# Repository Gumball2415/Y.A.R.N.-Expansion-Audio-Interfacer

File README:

# Y.A.R.N. Expansion Audio Interfacer

An Open-Source HardWare (OSHW) Famicom single expansion audio interfacer.

This project aims to allow a host cartridge to control an expansion audio cartridge's sound chip. This is a child of the S.C.A.R.F. project.

Currently a work in progress.

## PCB Specifications

W.I.P.

## License

- The PCB and schematics are licensed under the TAPR Open Hardware License ([www.tapr.org/OHL](http://www.tapr.org/OHL)).
- The PLD source code files are licensed under GPL 2.0 or higher. (https://www.gnu.org/licenses/old-licenses/gpl-2.0.html)
- © Persune 2021

## Credits

- lidnariq, grievre, Iyatemu, and plgDavid - advice, suggestions, general help
- lidnariq - providing advice for my schematics and addressing logic
- grievre - providing advice for my PCB design
- Special thanks to the NESDEV community, this project wouldn't have been possible without their extensive information and wiki!

## Support

Support me on [Ko-Fi](https://ko-fi.com/persune) to help me afford hardware development equipment and further improve this project!

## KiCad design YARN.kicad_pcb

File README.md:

# Y.A.R.N. Expansion Audio Interfacer

An Open-Source HardWare (OSHW) Famicom single expansion audio interfacer.

## About

This project aims to allow a host cartridge to control an expansion audio cartridge's sound chip through selected audio registers. This is a child of the S.C.A.R.F. project.

The principle is that the Main cartridge is expected to contain everything the NSF or program needs, with the audio solely being handled by the Exp audio cartridge.

This means that the expansion audio cartridge is write-only.

## Use

The Main cartridge is expected to contain mapper hardware that the NSF or program needs.

The Console is expected to not read the Exp. cartridge, but instead to write to registers the Exp. cartridge is expected to contain.

The Exp. cartridge must contain hardware that generates audio accessible by write-only registers that the Console expects.

If the Exp. cartridge contains VRC6B, toggle SW2 accordingly.

Do not toggle SW1, it is for prototyping purposes.

For Everdrives and flash carts: The flash cart UI (if it has one) may cause unwanted side effects if it is connected to YARN.

## PCB Specifications

- 2 layer PCB
- 1.2mm thickness
- ENIG-RoHS surface finish recommended; Gold fingers optional
- Beveled edge, chamfer cut
- Any soldermask color you want!

## License

- The PCB and schematics are licensed under the TAPR Open Hardware License ([www.tapr.org/OHL](http://www.tapr.org/OHL)).
- The S.C.A.R.F. Expansion Audio Interfacer Address Decoder ROM source code file is licensed under [MIT](https://mit-license.org/)
- © Persune 2022

## Credits

- lidnariq, grievre, Iyatemu, and plgDavid - advice, suggestions, general help
- lidnariq - providing advice for my schematics and addressing logic
- grievre - providing advice for my PCB design
- Special thanks to the NESDEV community, this project wouldn't have been possible without their extensive information and wiki!

## Support

If you enjoy this project or find it helpful, please support me on [Ko-Fi](https://ko-fi.com/persune) or [Patreon](https://www.patreon.com/persune)!

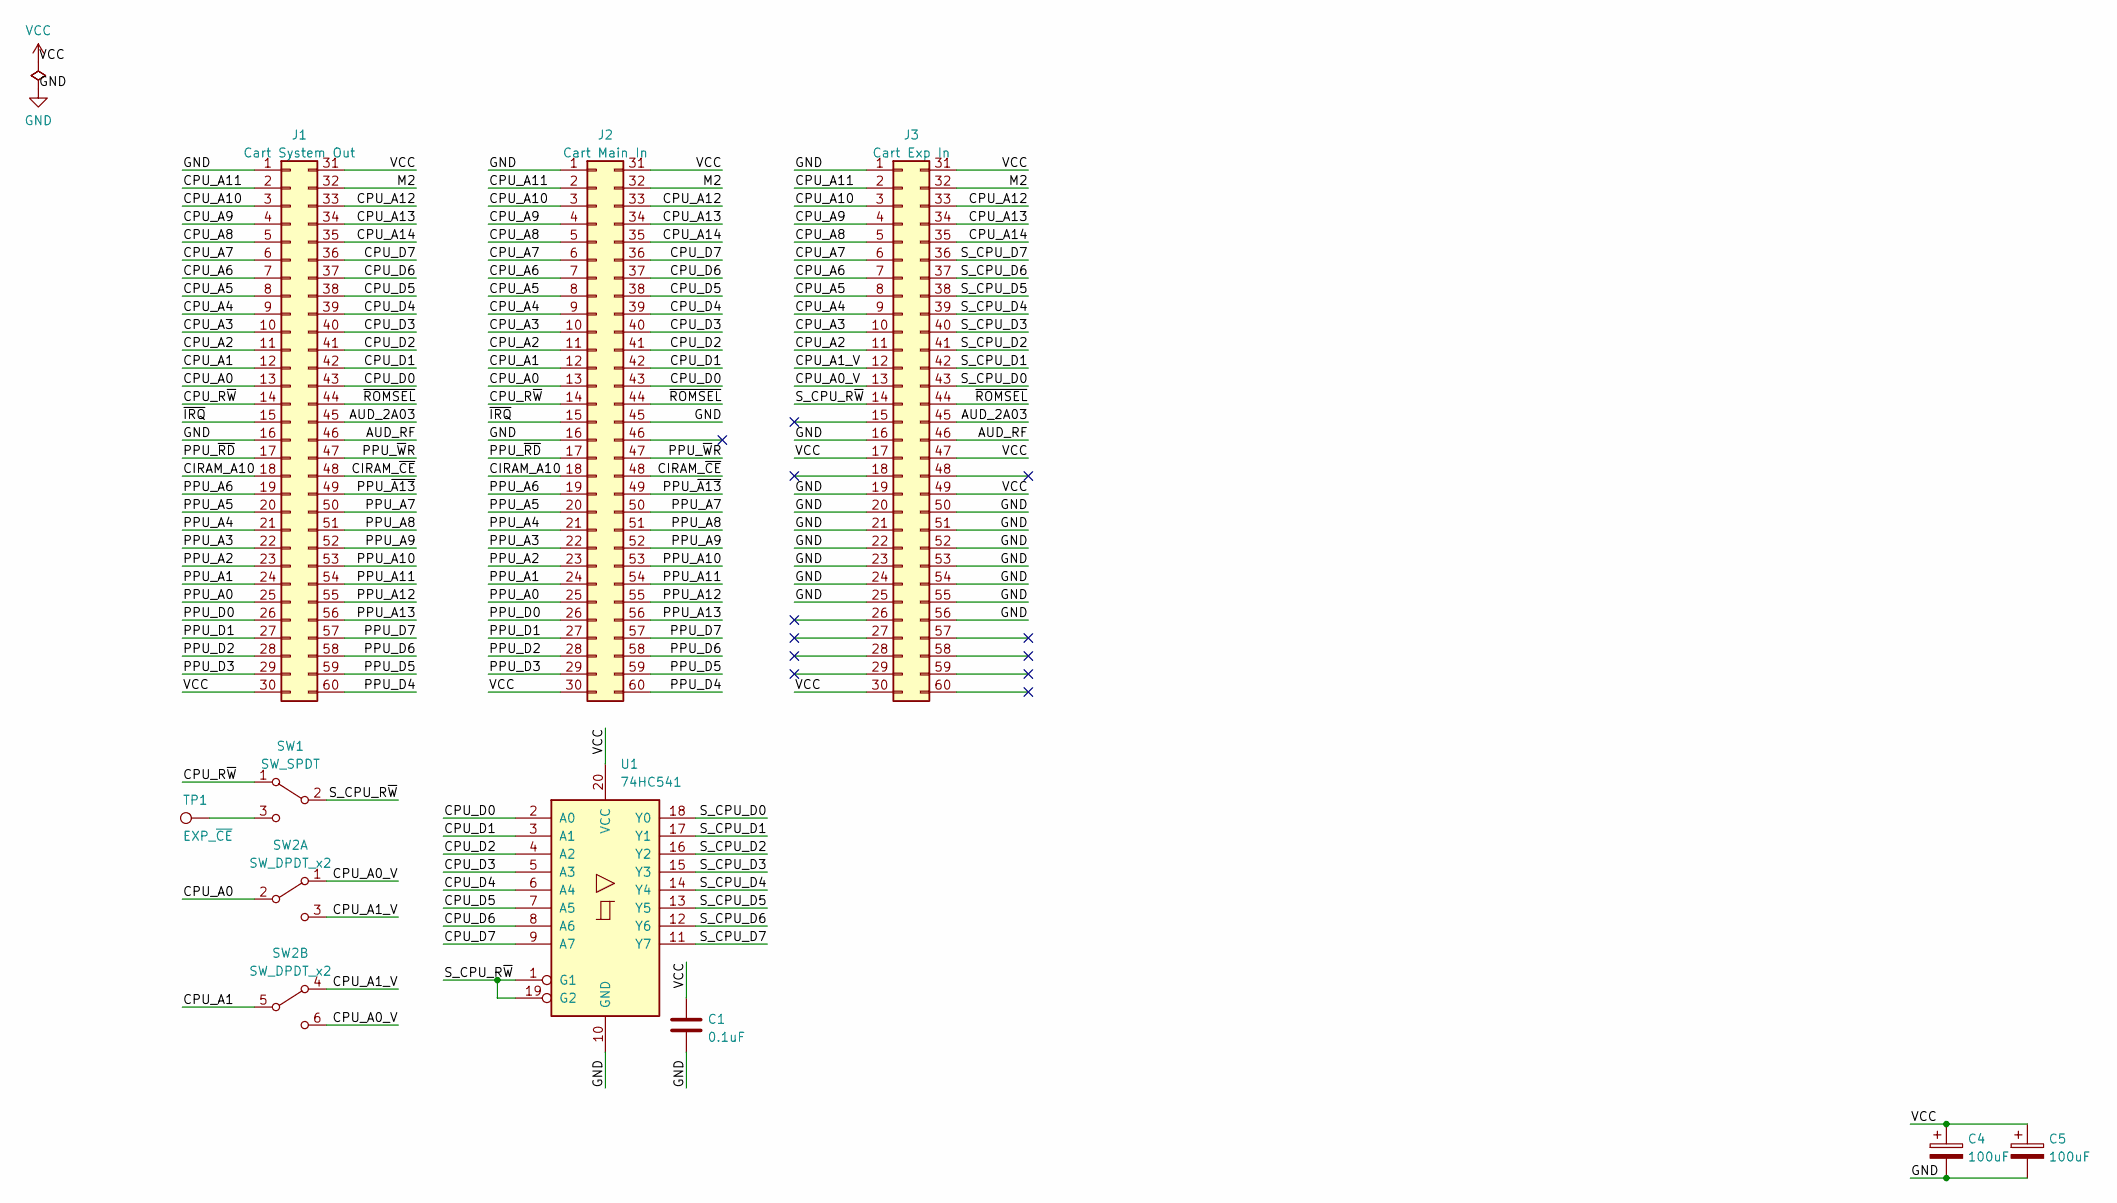
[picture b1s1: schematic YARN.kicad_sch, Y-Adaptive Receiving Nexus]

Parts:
C1: 0.1uF; C_Disc-0805_D3.0mm_W1.6mm_P2.50mm
C4, C5: 100uF; CP_Elec_6.3x5.4
J1: Cart System Out; HVC-ETROM-01
J2: Cart Main In; FC_CONN_F
J3: Cart Exp In; FC_CONN_F
SW1: SW_SPDT; SK-3390A-L0
SW2: SW_DPDT_x2; SS-3390S-L0
TP1: EXP_~{CE}; TestPoint_Pad_D2.0mm
U1: 74HC541; SOIC-20W_7.5x12.8mm_P1.27mm

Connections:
/AUD_2A03: J1.45, J3.45
/AUD_RF: J1.46, J3.46
/CIRAM_A10: J1.18, J2.18
/CIRAM_~CE: J1.48, J2.48
/CPU_A0: J1.13, J2.13, SW2.2 (B)
/CPU_A0_V: J3.13, SW2.1 (A), SW2.6 (C)
/CPU_A1: J1.12, J2.12, SW2.5 (B)
/CPU_A1_V: J3.12, SW2.3 (C), SW2.4 (A)
/CPU_A2: J1.11, J2.11, J3.11
/CPU_A3: J1.10, J2.10, J3.10
/CPU_A4: J1.9, J2.9, J3.9
/CPU_A5: J1.8, J2.8, J3.8
/CPU_A6: J1.7, J2.7, J3.7
/CPU_A7: J1.6, J2.6, J3.6
/CPU_A8: J1.5, J2.5, J3.5
/CPU_A9: J1.4, J2.4, J3.4
/CPU_A10: J1.3, J2.3, J3.3
/CPU_A11: J1.2, J2.2, J3.2
/CPU_A12: J1.33, J2.33, J3.33
/CPU_A13: J1.34, J2.34, J3.34
/CPU_A14: J1.35, J2.35, J3.35
/CPU_D0: J1.43, J2.43, U1.2 (A0)
/CPU_D1: J1.42, J2.42, U1.3 (A1)
/CPU_D2: J1.41, J2.41, U1.4 (A2)
/CPU_D3: J1.40, J2.40, U1.5 (A3)
/CPU_D4: J1.39, J2.39, U1.6 (A4)
/CPU_D5: J1.38, J2.38, U1.7 (A5)
/CPU_D6: J1.37, J2.37, U1.8 (A6)
/CPU_D7: J1.36, J2.36, U1.9 (A7)
/CPU_R~W: J1.14, J2.14, SW1.1 (A)
/M2: J1.32, J2.32, J3.32
/PPU_A0: J1.25, J2.25
/PPU_A1: J1.24, J2.24
/PPU_A2: J1.23, J2.23
/PPU_A3: J1.22, J2.22
/PPU_A4: J1.21, J2.21
/PPU_A5: J1.20, J2.20
/PPU_A6: J1.19, J2.19
/PPU_A7: J1.50, J2.50
/PPU_A8: J1.51, J2.51
/PPU_A9: J1.52, J2.52
/PPU_A10: J1.53, J2.53
/PPU_A11: J1.54, J2.54
/PPU_A12: J1.55, J2.55
/PPU_A13: J1.56, J2.56
/PPU_D0: J1.26, J2.26
/PPU_D1: J1.27, J2.27
/PPU_D2: J1.28, J2.28
/PPU_D3: J1.29, J2.29
/PPU_D4: J1.60, J2.60
/PPU_D5: J1.59, J2.59
/PPU_D6: J1.58, J2.58
/PPU_D7: J1.57, J2.57
/PPU_~A13: J1.49, J2.49
/PPU_~RD: J1.17, J2.17
/PPU_~WR: J1.47, J2.47
/S_CPU_D0: J3.43, U1.18 (Y0)
/S_CPU_D1: J3.42, U1.17 (Y1)
/S_CPU_D2: J3.41, U1.16 (Y2)
/S_CPU_D3: J3.40, U1.15 (Y3)
/S_CPU_D4: J3.39, U1.14 (Y4)
/S_CPU_D5: J3.38, U1.13 (Y5)
/S_CPU_D6: J3.37, U1.12 (Y6)
/S_CPU_D7: J3.36, U1.11 (Y7)
/S_CPU_R~W: J3.14, SW1.2 (B), U1.1 (G1), U1.19 (G2)
/~IRQ: J1.15, J2.15
/~ROMSEL: J1.44, J2.44, J3.44
GND: C1.2, C4.2, C5.2, J1.1, J1.16, J2.1, J2.16, J2.45, J3.1, J3.16, J3.19, J3.20, J3.21, J3.22, J3.23, J3.24, J3.25, J3.50, J3.51, J3.52, J3.53, J3.54, J3.55, J3.56, U1.10 (GND)
unnamed: SW1.3 (C), TP1.1
VCC: C1.1, C4.1, C5.1, J1.30, J1.31, J2.30, J2.31, J3.17, J3.30, J3.31, J3.47, J3.49, U1.20 (VCC)

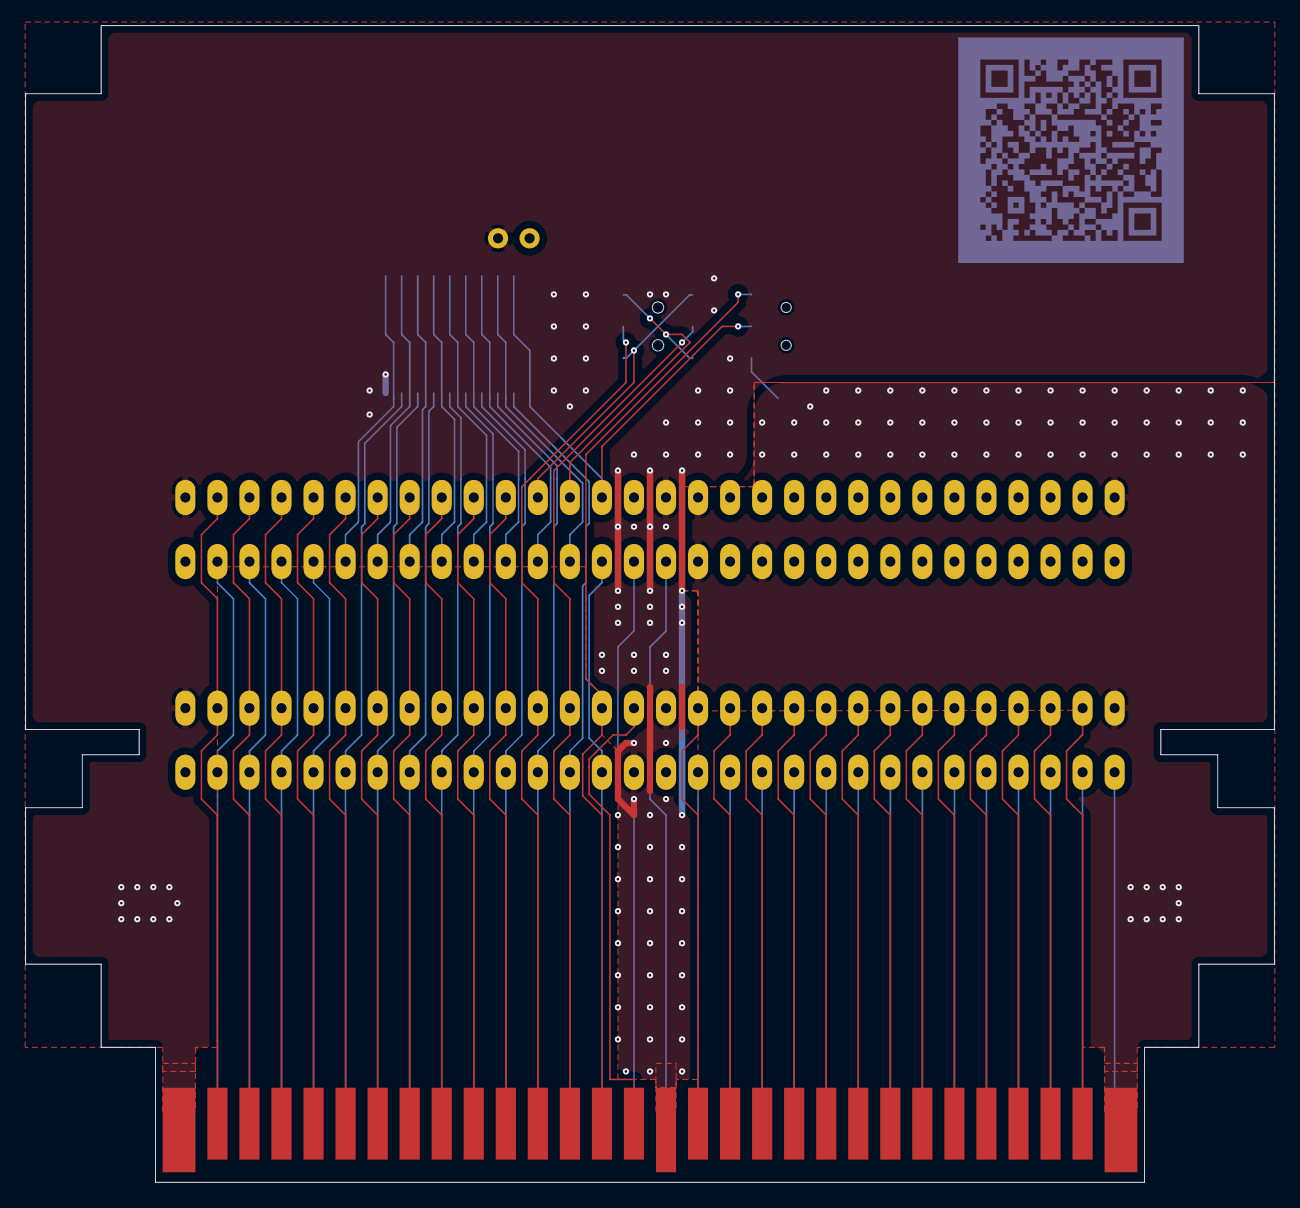
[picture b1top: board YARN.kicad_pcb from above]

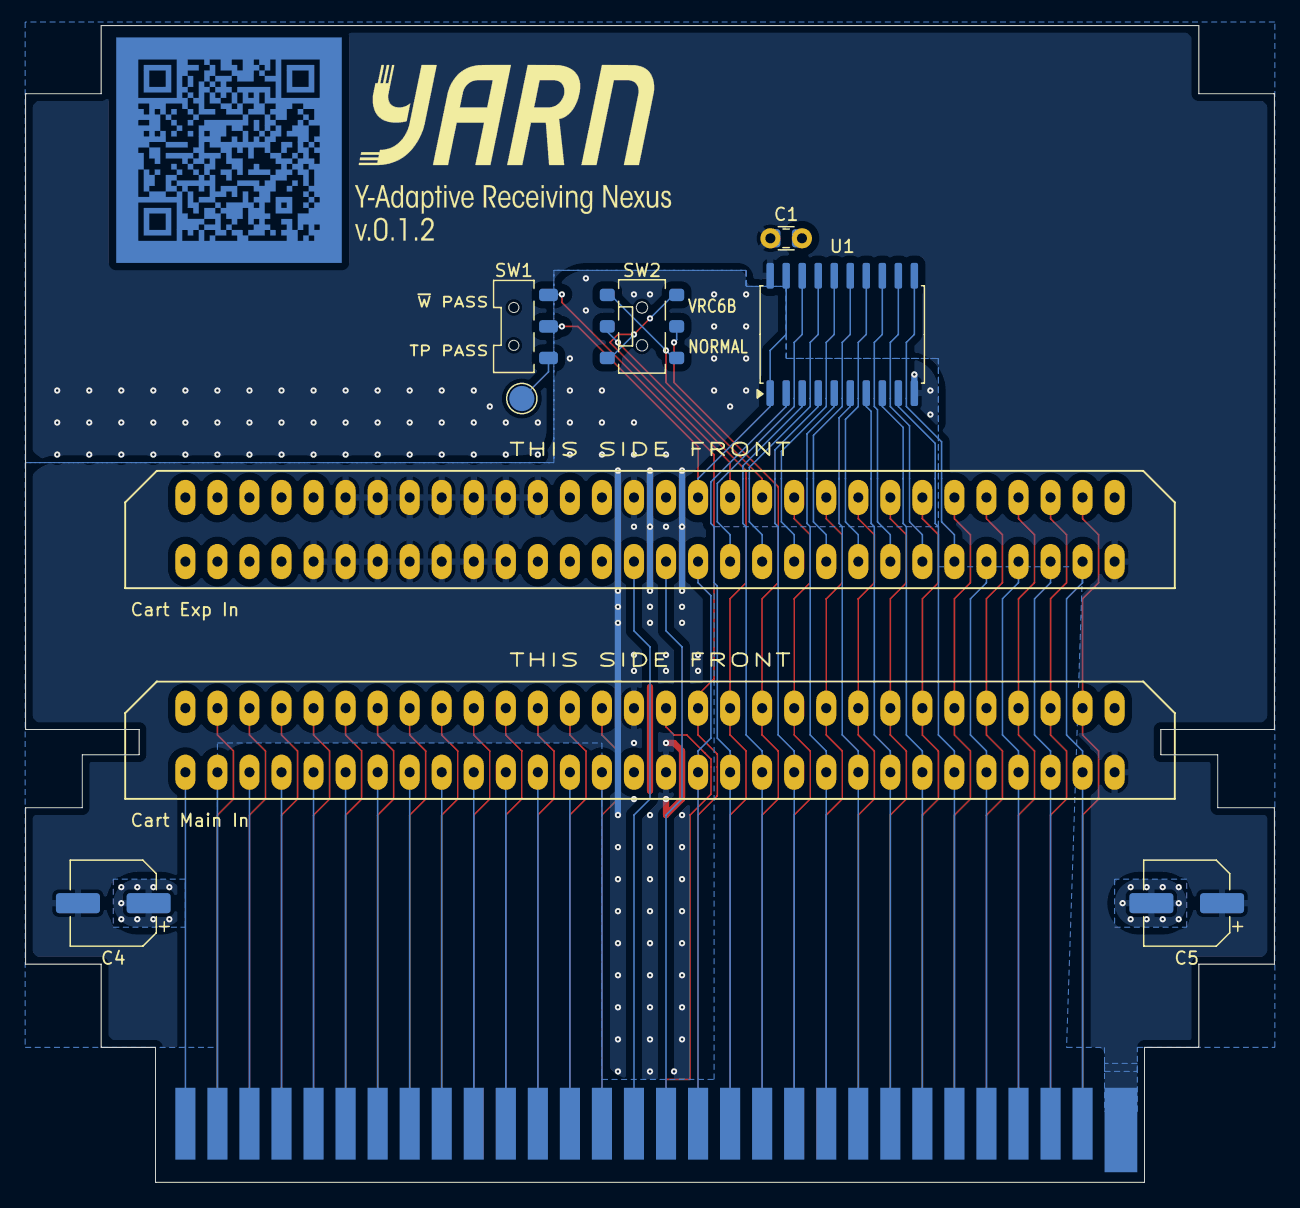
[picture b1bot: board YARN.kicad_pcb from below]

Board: 2 copper layers, 99.0 x 91.7 mm, 11 parts (10 on the bottom side), 70 nets.

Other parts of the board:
LOGO-2: YARN; YARN logo

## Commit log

2022-04-20 Add licence and readme
2022-04-20 Fix readme formatting
2022-11-13 Version 0.0.1
2022-11-14 Fix copper fills
2022-11-30 Add FUNDING.yml
2023-01-08 Use bus buffers instead of decoding logic
2023-03-01 Buffer data and addr bus, add switch for VRC6 A/B
2023-03-05 Improve slide switch footprints
2023-03-05 SS-3390S-L0 has slightly different dimensions
2023-04-05 Reword funding
2024-03-06 Redesign decoding architecture
    Thanks, lidnariq and Perkka!
